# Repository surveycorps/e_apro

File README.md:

e_apro
======

The electrical subsytems schematics, BOM, board files
- usb_hub is a 7 port usb hub based off of TI's TUSB2077A
- audio is a usb audio codec based off the PCM2912A
- gps is a usb powered gps module based off the Jupiter SE880
- screen is a hdmi to tft screen converter using TFP401A
- motor is a motor driver with F2V converters
- powers provides power regulator based off LM3478
- apro_lib contains all the custom symbols and footprints used
- eagle contains the files for connecting the various breakoutboards

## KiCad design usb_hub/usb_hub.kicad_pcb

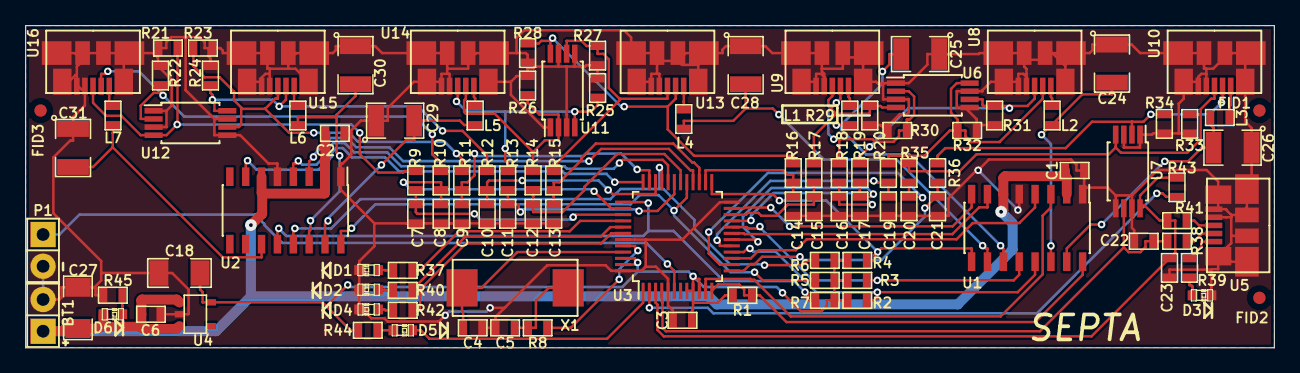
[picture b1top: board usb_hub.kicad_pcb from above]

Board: 2 copper layers, 100.0 x 25.8 mm, 111 parts (0 on the bottom side), 79 nets.

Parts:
BT1: BATTERY; Pin_Header_Straight_1x02
C1, C2, C6: 1uF; SMD-0603
C3: .1uF; SMD-0603
C4, C5: 33pF; SMD-0603
C7, C8, C9, C10, C11, C12, C13, C14, C15, C16, C17, C19, C20, C21, C22, C23: 22pF; SMD-0603
C18, C27: 10uF; SMD-1206
C24, C25, C26, C28, C29, C30, C31: 100uF; SMD-1210
D1, D2, D3, D4, D5, D6: LED; LED-0603
FID1, FID2, FID3: VAL**; SBA_FID
L1, L2, L3, L4, L5, L6, L7: FERRITE; SMD-0603
P1: CONN_01X02; Pin_Header_Straight_1x02
R1, R2, R3, R4, R5, R6, R7, R21, R22, R23, R24, R25, R26, R27, R28, R29, R30, R31, R32, R33, R34: 15k; SMD-0603
R8, R43: 1.5k; SMD-0603
R9, R10, R11, R12, R13, R14, R15, R16, R17, R18, R19, R20, R35, R36, R38, R41: 30; SMD-0603
R37, R39, R40, R42, R44, R45: 1k; SMD-0603
U1, U2: TPS2044B; SOIC-16_3.9x9.9mm_Pitch1.27mm
U3: TUSB2077A; TQFP-48_7x7mm_Pitch0.5mm
U4: TPS76333; SOT-23-5
U5: USB_A_MALE; MICRO_USB
U6, U7, U11, U12: SN75240; TSSOP-8_4.4x3mm_Pitch0.65mm
U8, U9, U10, U13, U14, U15, U16: USB_MICRO_OUT; MICRO_USB
X1: 6 MHz; FOX6MHZ

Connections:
3.3V: C3.1, C18.1, R1.1, R2.1, R3.1, R4.1, R5.1, R6.1, R7.1, R44.1, U3.8, U3.9, U3.10, U3.46, U3.47, U4.5
DM0: C22.1, R38.1, U3.4, U7.6
DM1: R34.2, R36.2, U7.2, U10.2
DM2: R20.2, R32.2, U6.8, U8.2
DM3: R18.2, R30.2, U6.2, U9.2
DM4: R16.2, R28.2, U11.8, U13.2
DM5: R14.2, R26.2, U11.2, U14.2
DM6: R12.2, R24.2, U12.8, U15.2
DM7: R10.2, R22.2, U12.2, U16.2
DP0: C23.1, R41.1, R43.2, U3.3, U7.8
DP0PUR: R43.1, U3.2
DP1: R33.2, R35.2, U7.4, U10.3
DP2: R19.2, R31.2, U6.6, U8.3
DP3: R17.2, R29.2, U6.4, U9.3
DP4: R15.2, R27.2, U11.6, U13.3
DP5: R13.2, R25.2, U11.4, U14.3
DP6: R11.2, R23.2, U12.6, U15.3
DP7: R9.2, R21.2, U12.4, U16.3
GND: BT1.2, C1.2, C2.2, C3.2, C4.2, C5.2, C6.2, C7.2, C8.2, C9.2, C10.2, C11.2, C12.2, C13.2, C14.2, C15.2, C16.2, C17.2, C18.2, C19.2, C20.2, C21.2, C22.2, C23.2, C24.1, C25.1, C26.1, C27.2, C28.1, C29.1, C30.1, C31.1, D1.2, D2.2, D3.2, D4.2, P1.2, R21.1, R22.1, R23.1, R24.1, R25.1, R26.1, R27.1, R28.1, R29.1, R30.1, R31.1, R32.1, R33.1, R34.1, R45.1, U1.1, U1.5, U2.1, U2.5, U3.5, U3.24, U3.43, U3.48, U4.2, U5.4, U5.5, U5.6, U6.1, U6.3, U6.5, U6.7, U7.1, U7.3, U7.5, U7.7, U8.4, U8.5, U8.6, U9.4, U9.5, U9.6, U10.4, U10.5, U10.6, U11.1, U11.3, U11.5, U11.7, U12.1, U12.3, U12.5, U12.7, U13.4, U13.5, U13.6, U14.4, U14.5, U14.6, U15.4, U15.5, U15.6, U16.4, U16.5, U16.6
HUBCFG: R37.1, U3.40
unnamed: C4.1, U3.45, X1.2
unnamed: C5.1, R8.2, X1.1
unnamed: C7.1, R9.1, U3.39
unnamed: C8.1, R10.1, U3.38
unnamed: C9.1, R11.1, U3.35
unnamed: C10.1, R12.1, U3.34
unnamed: C11.1, R13.1, U3.31
unnamed: C12.1, R14.1, U3.30
unnamed: C13.1, R15.1, U3.27
unnamed: C14.1, R16.1, U3.26
unnamed: C15.1, R17.1, U3.22
unnamed: C16.1, R18.1, U3.21
unnamed: C17.1, R19.1, U3.18
unnamed: C19.1, R20.1, U3.17
unnamed: C20.1, R35.1, U3.14
unnamed: C21.1, R36.1, U3.13
unnamed: D1.1, R37.2
unnamed: D2.1, R40.2
unnamed: D3.1, R39.1
unnamed: D4.1, R42.2
unnamed: D5.1, R44.2
unnamed: D6.2, R45.2
unnamed: L1.2, U9.1
unnamed: L2.2, U8.1
unnamed: L3.2, U10.1
unnamed: L4.2, U13.1
unnamed: L5.2, U14.1
unnamed: L6.2, U15.1
unnamed: L7.2, U16.1
unnamed: R8.1, U3.44
unnamed: R38.2, U5.2
unnamed: R39.2, U5.1
unnamed: R41.2, U5.3
OC1: R1.2, U1.16, U3.12
OC2: R2.2, U1.13, U3.16
OC3: R3.2, U1.12, U3.20
OC4: R4.2, U1.9, U3.25
OC5: R5.2, U2.16, U3.29
OC6: R6.2, U2.13, U3.33
OC7: R7.2, U2.12, U3.37
OUT1: C26.2, L3.1, U1.15
OUT2: C24.2, L2.1, U1.14
OUT3: C25.2, L1.1, U1.11
OUT4: C28.2, L4.1, U1.10
OUT5: C29.2, L5.1, U2.15
OUT6: C30.2, L6.1, U2.14
OUT7: C31.2, L7.1, U2.11
PORTDIS: R42.1, U3.42
PORTPWR: R40.1, U3.41
PWRON1: U1.3, U3.11
PWRON2: U1.4, U3.15
PWRON3: U1.7, U3.19
PWRON4: U1.8, U3.23
PWRON5: U2.3, U3.28
PWRON6: U2.4, U3.32
PWRON7: U2.7, U3.36
RST: P1.1, U3.6
SPND: D5.2, U3.1
VCC: BT1.1, C1.1, C2.1, C6.1, C27.1, D6.1, U1.2, U1.6, U2.2, U2.6, U4.1, U4.3

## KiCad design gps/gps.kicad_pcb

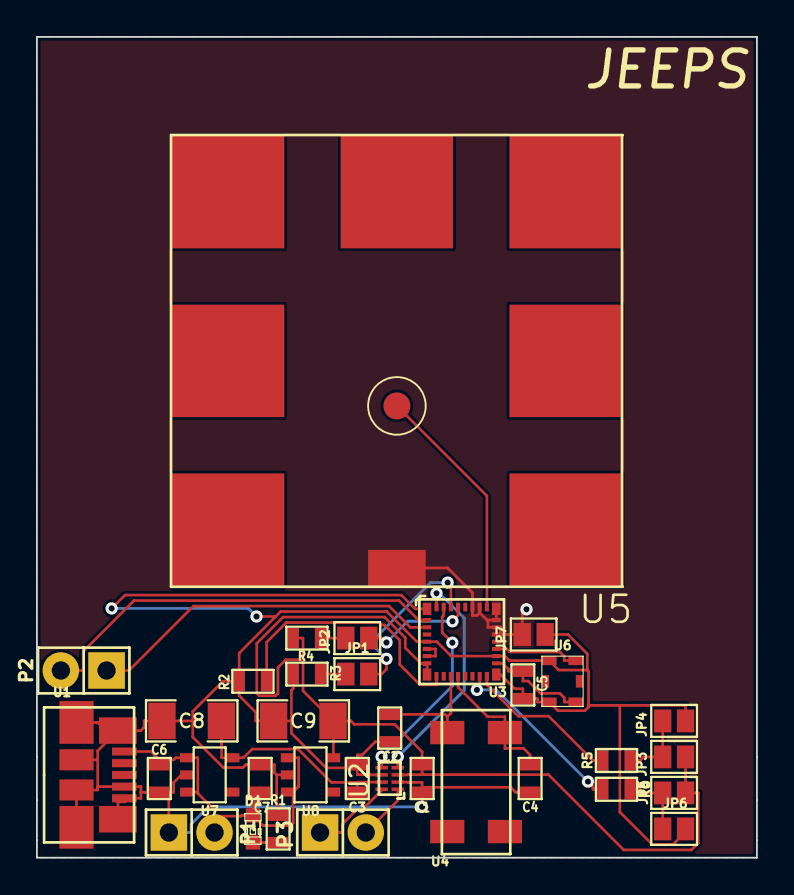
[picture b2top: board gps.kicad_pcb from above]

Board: 2 copper layers, 40.0 x 45.6 mm, 34 parts (0 on the bottom side), 27 nets.

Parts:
C1, C3, C5: .1uF; SMD-0603
C2: 18pF; SMD-0603
C4: 22pF; SMD-0603
C6, C7: 1uF; SMD-0603
C8, C9: 10uF; SMD-1206
D1: LED; LED-0603
JP1, JP2, JP3, JP4, JP5, JP6, JP7: JUMPER; GS2
P1: PWR; Pin_Header_Straight_1x02
P2: CTL; Pin_Header_Straight_1x02
P3: UART; Pin_Header_Straight_1x02
R1: 1k; SMD-0603
R2, R3: 100k; SMD-0603
R4, R5: 10k; SMD-0603
R6: 6k; SMD-0603
U1: USB_A_FEMALE; MICRO_USB
U2: TXS0102
U3: SE880
U4: ABS25
U5: SGP25C
U6: KT2520
U7: TPS76333; SOT-23-5
U8: TPS76318; SOT-23-5

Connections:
1.8V: C1.1, C9.1, JP3.2, JP5.2, R4.1, U2.3, U3.8, U3.9, U8.5
3.3V: C3.1, C8.1, U2.7, U7.5
5V: C6.1, C7.1, D1.1, P1.2, U1.1, U7.1, U7.3, U8.1, U8.3
/50ohm: U3.27, U5.1
AGND: JP7.1, U3.23, U3.24, U3.25, U3.26, U3.28, U3.29, U5.2
DGND: C1.2, C2.2, C3.2, C4.2, C5.2, C6.2, C7.2, C8.2, C9.2, JP4.2, JP6.2, JP7.2, P1.1, R1.2, R2.2, R3.2, U1.4, U1.5, U1.6, U2.2, U2.6, U3.1, U3.5, U3.18, U3.20, U6.1, U6.3, U7.2, U8.2
unnamed: C2.1, U3.12, U4.1
unnamed: C4.1, U3.13, U4.4
unnamed: C5.1, U3.19, U6.6
unnamed: D1.2, R1.1
unnamed: JP1.1, R3.1
unnamed: JP1.2, U3.32
unnamed: JP2.1, R4.2
unnamed: JP2.2, U3.31
unnamed: JP3.1, JP4.1, R5.1
unnamed: JP5.1, JP6.1, R6.1
unnamed: R2.1, U3.10
unnamed: R5.2, U3.17
unnamed: R6.2, U3.16
unnamed: U2.4, U3.34
unnamed: U2.5, U3.33
unnamed: U3.6, U3.7
unnamed: U3.21, U6.4
ON_OFF: P2.1, U3.3
RX: P3.2, U2.1
SYSTEM_ON: P2.2, U3.2
TX: P3.1, U2.8

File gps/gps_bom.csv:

Item,Qty,Reference(s),Value,LibPart,Footprint,Datasheet
1,5,"C1, C10, C11, C3, C5",.1uF,device:Csmall,SMD_Packages:SMD-0603,
2,1,C2,18pF,device:Csmall,SMD_Packages:SMD-0603,
3,1,C4,22pF,device:Csmall,SMD_Packages:SMD-0603,
4,2,"C6, C7",1uF,device:Csmall,SMD_Packages:SMD-0603,
5,2,"C8, C9",10uF,device:Csmall,SMD_Packages:SMD-0603,
6,1,D1,LED(G),device:LED,LEDs:LED-0603,
7,7,"JP1, JP2, JP3, JP4, JP5, JP6, JP7",JUMPER,device:JUMPER,Connect:GS2,
8,1,P1,PWR,conn:CONN_01X02,Pin_Headers:Pin_Header_Straight_1x02,
9,1,P2,CTL,conn:CONN_01X02,Pin_Headers:Pin_Header_Straight_1x02,
10,1,P3,UART,conn:CONN_01X02,Pin_Headers:Pin_Header_Straight_1x02,
11,1,R1,510,device:R,SMD_Packages:SMD-0603,
12,2,"R2, R3",100k,device:R,SMD_Packages:SMD-0603,
13,3,"R4, R5, R7",10k,device:R,SMD_Packages:SMD-0603,
14,1,R6,6k,device:R,SMD_Packages:SMD-0603,
15,1,U1,USB_A_FEMALE,gps-cache:USB_A_FEMALE,ab2_usb:AB2_USB_MICRO_SMD,
16,1,U2,TXS0102,gps:TXS0102,gps:TXS0102,
17,1,U3,SE880,gps:SE880,gps:SE880,
18,1,U4,ABS25,gps:ABS25,gps:ABS25,
19,1,U5,SGP25C,gps:SGP25C,gps:SGP25C,
20,1,U6,KT2520,gps:KT2520,gps:KT2520,
21,1,U7,TPS76333,gps:TPS76318,SMD_Packages:SOT-23-5,
22,1,U8,TPS76318,gps:TPS76318,SMD_Packages:SOT-23-5,

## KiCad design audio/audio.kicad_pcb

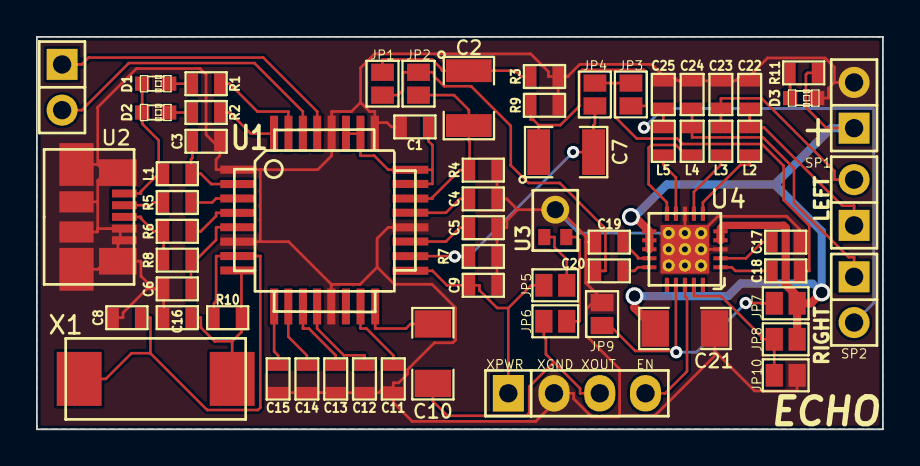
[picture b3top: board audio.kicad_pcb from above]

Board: 2 copper layers, 47.0 x 21.8 mm, 64 parts (0 on the bottom side), 52 nets.

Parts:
C1, C3, C4, C5, C6, C11, C17, C18, C19, C20: 1uF; SMD-0603
C2, C7: 100uF; SMD-1210
C8, C16: 33pF; SMD-0603
C9, C12: .1uF; SMD-0603
C10, C21: 10uF; SMD-1206
C13: 3.3uF; SMD-0603
C14, C15: 100pF; SMD-0603
C22, C23, C24, C25: 1nF; SMD-0603
D1, D2, D3: GREEN; LED-0603
JP1, JP2, JP3, JP4, JP5, JP6, JP7, JP8, JP9, JP10: JUMPER; GS2
L1: 1uH; SMD-0603
L2, L3, L4, L5: FERRITE; SMD-0603
P1, P3: CONN_02X01; Pin_Header_Straight_2x01
P2: CONN_01X04; Pin_Header_Straight_1x04
R1, R2, R11: 1k; SMD-0603
R3, R4, R7, R9: 3K3; SMD-0603
R5, R6: 30R; SMD-0603
R8: 1K5; SMD-0603
R10: 1M; SMD-0603
SP1, SP2: SPEAKER; Pin_Header_Straight_2x01
U1: PCM2912A; TQFP-32
U2: USB_A_MALE; MICRO_USB
U3: MIC
U4: TPA2017D2
X1: 6MHz; FOX6MHZ

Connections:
+5VA: C21.2, JP7.1, JP8.1, P3.1, R11.2, U4.4, U4.5, U4.11, U4.12, U4.13
EN: P2.4, U4.18
L_IN: C18.2, JP3.1, JP4.2
unnamed: C1.1, U1.23, U1.24, U1.26, U1.27
unnamed: C2.1, JP1.2, R3.2
unnamed: C2.2, JP2.1, R4.2, U1.22
unnamed: C3.1, L1.1, U1.2
unnamed: C4.2, U1.21
unnamed: C5.2, U1.19
unnamed: C6.2, R8.1, U1.5
unnamed: C7.1, JP4.1, R9.1
unnamed: C7.2, JP3.2, R7.1, U1.18
unnamed: C8.1, R10.2, U1.7, X1.1
unnamed: C10.2, U1.16
unnamed: C11.1, U1.15
unnamed: C12.2, U1.12
unnamed: C13.2, U1.11
unnamed: C14.2, U1.10
unnamed: C15.2, U1.9
unnamed: C16.1, R10.1, U1.8, X1.2
unnamed: C17.1, U4.2
unnamed: C18.1, U4.1
unnamed: C19.1, U4.14
unnamed: C20.1, U4.15
unnamed: C22.2, L2.2, SP1.1
unnamed: C23.2, L3.2, SP1.2
unnamed: C24.2, L4.2, SP2.1
unnamed: C25.2, L5.2, SP2.2
unnamed: D1.1, D2.1, L1.2, U2.1
unnamed: D1.2, R1.2
unnamed: D2.2, R2.2
unnamed: D3.1, R11.1
unnamed: JP5.2, U3.3
unnamed: JP6.2, U3.1
unnamed: JP7.2, JP9.2, U4.17
unnamed: JP8.2, JP10.2, U4.19
unnamed: L2.1, U4.6
unnamed: L3.1, U4.7
unnamed: L4.1, U4.10
unnamed: L5.1, U4.9
unnamed: P1.1, U1.29
unnamed: P1.2, U1.30
unnamed: R1.1, U1.31
unnamed: R2.1, U1.32
unnamed: R5.1, U1.3
unnamed: R5.2, U2.2
unnamed: R6.1, U1.4
unnamed: R6.2, R8.2, U2.3
R_IN: C20.2, JP1.1, JP2.2
XGND: C1.2, C3.2, C4.1, C5.1, C6.1, C8.2, C9.1, C11.2, C12.1, C13.1, C14.1, C15.1, C16.2, C17.2, C19.2, C21.1, C22.1, C23.1, C24.1, C25.1, D3.2, JP9.1, JP10.1, P2.2, P3.2, R3.1, R4.1, R7.2, R9.2, U1.1, U1.6, U1.13, U1.20, U1.25, U1.28, U2.4, U2.5, U2.6, U3.2, U4.3, U4.8, U4.21
XOUT: C10.1, JP6.1, P2.3
XPWR: C9.2, JP5.1, P2.1, U1.17

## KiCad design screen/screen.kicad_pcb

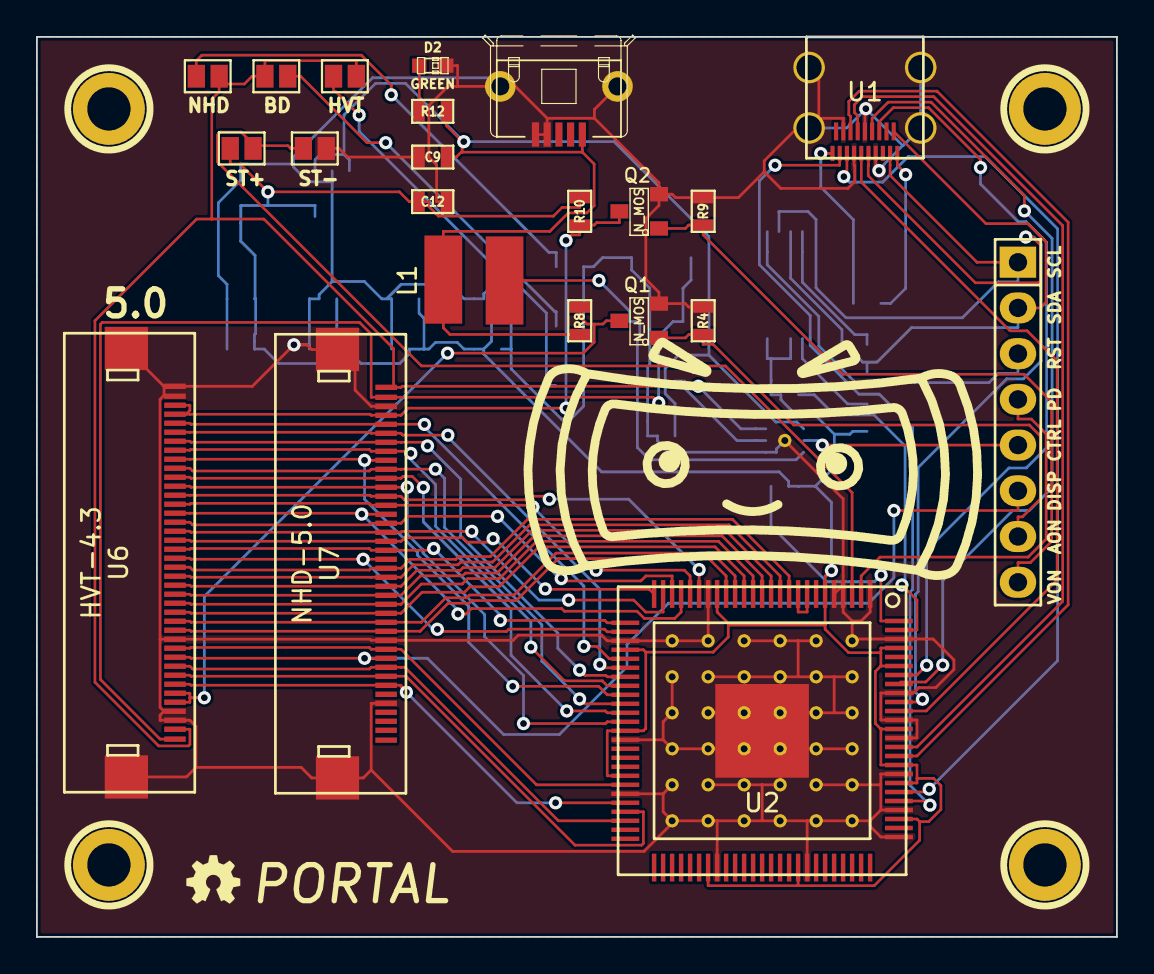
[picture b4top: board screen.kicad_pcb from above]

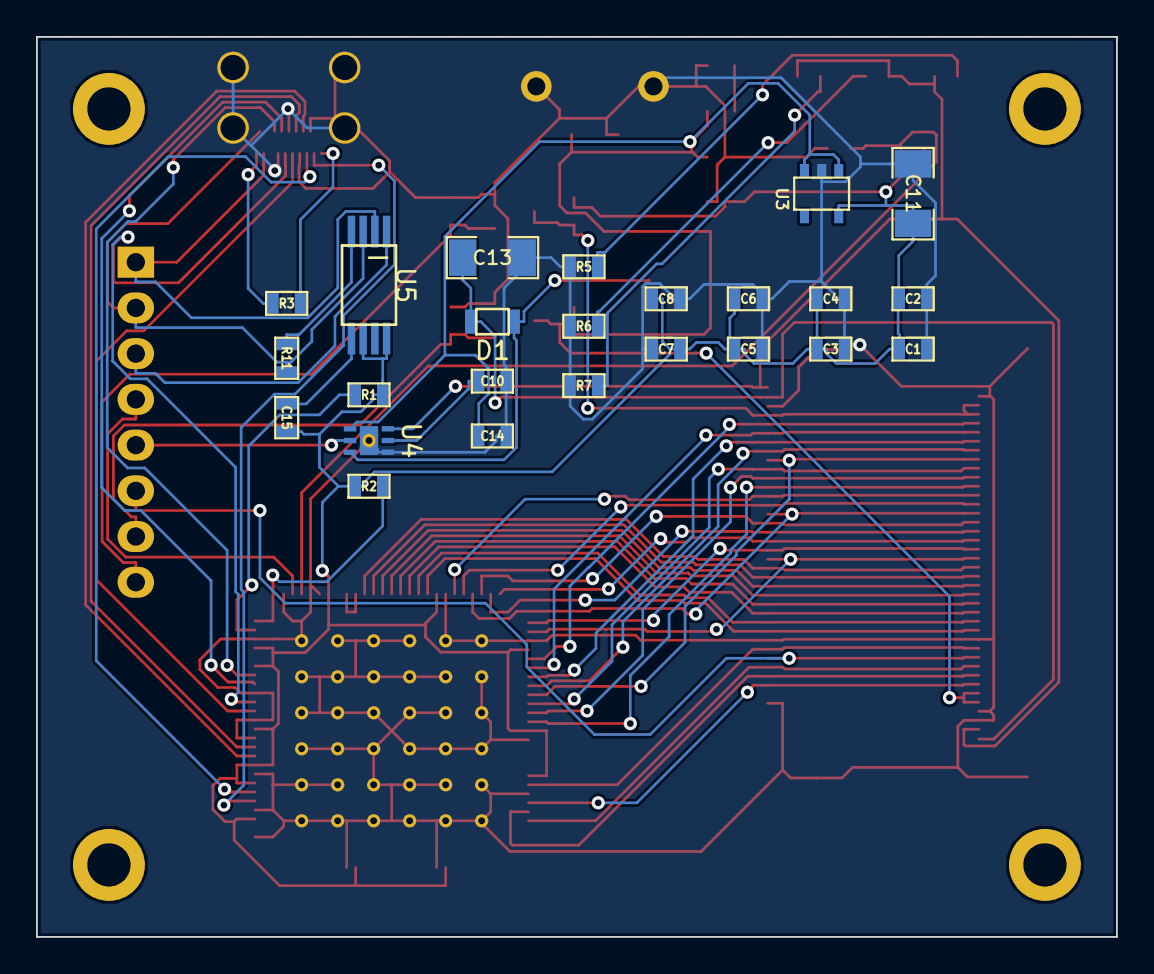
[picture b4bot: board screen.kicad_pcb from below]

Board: 2 copper layers, 60.0 x 50.0 mm, 52 parts (24 on the bottom side), 65 nets.

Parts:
1PIN, 2PIN, 3PIN, 4PIN: P***; 1pin
C1, C2, C3, C4: 22uF; SMD-0603
C5, C6, C7, C8, C12, C15: 0.1uF; SMD-0603
C9: 1uF; SMD-0603
C10: 0.22uF; SMD-0603
C11, C13: 10uF; SMD-1206
C14: 4.7uF; SMD-0603
D1: DIODESCH; SOD323
D2: GREEN; LED-0603
G1: LOGO; OSLOGO
G2: LOGO
JP1: NHD; GS2
JP2: BD; GS2
JP3: HVT; GS2
JP4: ST+; GS2
JP5: ST-; GS2
L1: 22uH; VLCF5020
P1: CONN_01X08; Pin_Header_Straight_1x08
Q1, Q2: N_MOS; SOT-23
R1, R2, R3: 4.7k; SMD-0603
R4, R8, R9, R10: 10k; SMD-0603
R5: 3.32R; SMD-0603
R6: 4.99R; SMD-0603
R7: 10R; SMD-0603
R11: 1k; SMD-0603
R12: 510R; SMD-0603
U1: uHDMI
U2: TFP401A
U3: TPS76333; SOT-23-5
U4: TSP61161
U5: M93C46; TSSOP8
U6: HVT-4.3; 40_PIN
U7: NHD-5.0; 40_PIN
USB1: AB2_USB; AB2_USB_MICRO_SMD

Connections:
3.3V: C1.2, C2.2, C3.2, C4.2, C5.2, C6.2, C7.2, C8.2, C11.1, C12.1, C15.1, JP4.2, R1.2, R2.2, R10.2, U2.6, U2.18, U2.29, U2.38, U2.43, U2.57, U2.67, U2.78, U2.82, U2.84, U2.88, U2.95, U2.97, U3.5, U5.6, U5.8
AVDD: Q1.3, R8.1, U6.35, U6.36
A_ON: P1.7, Q1.1, R4.1
BLUE0: U2.10, U6.21, U7.21
BLUE1: U2.11, U6.22, U7.22
BLUE2: U2.12, U6.23, U7.23
BLUE3: U2.13, U6.24, U7.24
BLUE4: U2.14, U6.25, U7.25
BLUE5: U2.15, U6.26, U7.26
BLUE6: U2.16, U6.27, U7.27
BLUE7: U2.17, U6.28, U7.28
CK: U2.44, U6.30, U7.30
CTRL: P1.5, U4.5
DE: U2.46, U6.34, U7.34
DISP: P1.6, U6.31, U7.31
GND: C1.1, C2.1, C3.1, C4.1, C5.1, C6.1, C7.1, C8.1, C9.2, C10.2, C11.2, C12.2, C13.2, C14.2, D2.2, JP5.2, Q1.2, Q2.2, R4.2, R5.2, R6.2, R7.2, R9.2, U1.4, U1.7, U1.10, U1.13, U1.20, U1.21, U1.22, U1.23, U2.1, U2.4, U2.5, U2.19, U2.28, U2.39, U2.45, U2.58, U2.68, U2.76, U2.79, U2.83, U2.87, U2.89, U2.92, U2.98, U2.101, U3.2, U4.3, U4.7, U6.1, U6.2, U6.29, U6.37, U6.38, U6.41, U6.42, U7.3, U7.29, U7.36, U7.41, U7.42, USB1.4, USB1.5, USB1.6
GREEN0: U2.20, U6.13, U7.13
GREEN1: U2.21, U6.14, U7.14
GREEN2: U2.22, U6.15, U7.15
GREEN3: U2.23, U6.16, U7.16
GREEN4: U2.24, U6.17, U7.17
GREEN5: U2.25, U6.18, U7.18
GREEN6: U2.26, U6.19, U7.19
GREEN7: U2.27, U6.20, U7.20
HDMI_5V: R3.1, U1.19
HSYNC: U2.48, U6.32, U7.32
LED+: C13.1, D1.2, U6.40, U7.2
LED-: JP1.2, JP2.2, JP3.2, U4.1, U6.39, U7.1
unnamed: C10.1, U4.2
unnamed: C15.2, U5.5
unnamed: D1.1, L1.2, U4.4
unnamed: D2.1, R12.1
unnamed: JP1.1, R5.1
unnamed: JP2.1, R6.1
unnamed: JP3.1, R7.1
unnamed: R1.1, U2.99
unnamed: R2.1, U2.100
unnamed: R3.2, U1.1
unnamed: R11.1, U5.4
unnamed: U2.8, U2.9
PD: P1.4, U2.2
RED0: U2.30, U6.5, U7.5
RED1: U2.31, U6.6, U7.6
RED2: U2.32, U6.7, U7.7
RED3: U2.33, U6.8, U7.8
RED4: U2.34, U6.9, U7.9
RED5: U2.35, U6.10, U7.10
RED6: U2.36, U6.11, U7.11
RED7: U2.37, U6.12, U7.12
RST: P1.3, U5.1
RX0+: U1.9, U2.90
RX0-: U1.11, U2.91
RX1+: U1.6, U2.85
RX1-: U1.8, U2.86
RX2+: U1.3, U2.80
RX2-: U1.5, U2.81
RXC+: U1.12, U2.93
RXC-: U1.14, U2.94
SCL_BB: P1.1, U1.17, U5.2
SDA_BB: P1.2, R11.2, U1.18, U5.3
ST: JP4.1, JP5.1, U2.3
VBUS: C9.1, C14.1, L1.1, R8.2, R12.2, U3.1, U3.3, U4.6, USB1.1
VDD: Q2.3, R10.1, U6.3, U6.4, U7.4
VSYNC: U2.47, U6.33, U7.33
V_ON: P1.8, Q2.1, R9.1

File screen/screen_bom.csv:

Item,Qty,Reference(s),Value,LibPart,Footprint,Datasheet
1,4,"C1, C2, C3, C4",22uF,device:Csmall,SMD_Packages:SMD-0603,
2,1,C10,0.22uF,device:Csmall,SMD_Packages:SMD-0603,
3,2,"C11, C13",10uF,device:Csmall,SMD_Packages:SMD-1206,
4,6,"C12, C15, C5, C6, C7, C8",0.1uF,device:Csmall,SMD_Packages:SMD-0603,
5,1,C14,4.7uF,device:Csmall,SMD_Packages:SMD-0603,
6,1,C9,1uF,device:Csmall,SMD_Packages:SMD-0603,
7,1,D1,DIODESCH,device:DIODESCH,SCREEN:SOD323,
8,1,D2,GREEN,device:LED,LEDs:LED-0603,
9,1,JP1,NHD,device:JUMPER,Connect:GS2,
10,1,JP2,BD,device:JUMPER,Connect:GS2,
11,1,JP3,HVT,device:JUMPER,Connect:GS2,
12,1,JP4,ST+,device:JUMPER,Connect:GS2,
13,1,JP5,ST-,device:JUMPER,Connect:GS2,
14,1,L1,22uH,device:INDUCTOR,SCREEN:VLCF5020,
15,1,P1,CONN_01X08,conn:CONN_01X08,Pin_Headers:Pin_Header_Straight_1x08,
16,2,"Q1, Q2",N_MOS,screen:N_MOS,SMD_Packages:SOT-23,
17,3,"R1, R2, R3",4.7k,screen:Rsmall,SMD_Packages:SMD-0603,
18,4,"R10, R4, R8, R9",10k,screen:Rsmall,SMD_Packages:SMD-0603,
19,1,R11,1k,screen:Rsmall,SMD_Packages:SMD-0603,
20,1,R12,510R,screen:Rsmall,SMD_Packages:SMD-0603,
21,1,R5,3.32R,screen:Rsmall,SMD_Packages:SMD-0603,
22,1,R6,4.99R,screen:Rsmall,SMD_Packages:SMD-0603,
23,1,R7,10R,screen:Rsmall,SMD_Packages:SMD-0603,
24,1,U1,uHDMI,screen:uHDMI,SCREEN:uHDMI,
25,1,U2,TFP401A,screen:TFP401A,SCREEN:TFP401A,
26,1,U3,TPS76333,screen:TPS76333,SMD_Packages:SOT-23-5,
27,1,U4,TSP61161,screen:TSP61161,SCREEN:TSP61161,
28,1,U5,M93C46,usb_hub:M93C46,SCREEN:TSSOP8,
29,1,U6,HVT-4.3,screen:HVT-4.3,SCREEN:40_PIN,
30,1,U7,NHD-5.0,screen:NHD-5.0,SCREEN:40_PIN,
31,1,USB1,AB2_USB,ab2_usb:AB2_USB,MICRO_USB:AB2_USB_MICRO_SMD,

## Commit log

2014-09-16 added pdf of schematic
2014-09-20 crystal and ferrite bead
2014-09-20 crystals and ferrite beads for real this time
2014-09-21 started external mic board and audio pcb
2014-09-21 started pcb design for usb hub
2014-09-22 need to not waste as much space on board
2014-09-22 audio pcb updates
2014-09-23 made thinner approx 1x4
2014-09-23 finishing audio pcb layout
2014-09-23 updating readme file
2014-09-24 added logo mod, updated audio pcb, and finished micboard
2014-09-24 finished the usb_hub
2014-09-25 intial commit for gps module
2014-09-26 updating audio board to change vias
2014-09-26 correcting audio board vias
2014-09-27 added the TFP401A symbol
2014-09-27 now using the SE880 GPS
2014-09-28 finished gps schematic. need to create footprints
2014-09-28 added logo image
2014-09-29 made most of the gps footprints
2014-09-30 usb_hub ready for manufacturing
2014-09-30 finalizing audio board
2014-09-30 usb_hub final. fixed annular ring clearance
2014-09-30 moved the trace away from the edge
2014-10-01 finished the gps schematic. need to finish BOM. Preliminary work on board
2014-10-01 changed mic. board done...i hope
2014-10-01 board is ready
2014-10-04 added jumpers to switch communication method
2014-10-06 initial commit of screen schematic
2014-10-07 fixed pin 47 to gnd. need to clip and solder to adjacent pin
2014-10-07 need to place all components on bottom and create analog ground plane for antenna
2014-10-07 fixed the bom so it shows up nicely
2014-10-07 finishing up schematic and starting board footprints and design
2014-10-08 modeled the 50ohm trace as grounded coplanar. need to move things around better so it can solve
2014-10-08 finished component modules and started screen board design
2014-10-09 moving around some stuff for routing
2014-10-11 fixed audio bom
2014-10-11 added usb_hub bom
2014-10-16 finished routing. need to add stitching vias
2014-10-17 screen board is complete
2014-10-17 added bom
2014-10-19 Finished the GPS module
2014-10-19 Finished usb_hub revision B. Less complex, less that can go wrong
2014-10-19 started motor driver schematic
2014-10-19 removing extra readme
2014-10-28 finalizing components for 5v5a
2014-10-28 motor schematic almost finished
2014-11-03 started design for pick and place
2014-11-04 Moving all the symbols and footprints in a common library. Changed a few components so we have less reels to buy for pick and place. Changing amplifier to a more supported one from TI.
2014-11-06 finished routing. need to check bom and trace widths and pos file
2014-11-10 usb_hub ready for review. Audio schematic in the works
2014-11-10 need to add required fields for assembly
2014-11-11 sent usb_hub for review. Finished gps schematic/bom.
2014-11-12 adding fields to audio schematic
2014-11-13 finished schematic. need to route board and send BOM
2014-11-14 finished board layout. Ready for review
2014-11-14 placed all components on one side to make assembly easier. Ready for review
2014-11-14 Need to route the 50ohm trace
2014-11-15 cleaned up the usb hub project. waiting quote on elecrow
2015-03-20 added eagle files that are used to connect the various store bought breakout boards so that we can finish the project on time
